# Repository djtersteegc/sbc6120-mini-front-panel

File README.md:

Project thread at https://forum.vcfed.org/index.php?threads/sbc6120-mini-front-panel.1245272/

# Switches

The current PCB and dress panel are drilled for miniature toggles with a 6mm diameter bushing/stem.  1/4-40 switches will NOT fit since I wanted a tight fit on the dress panel and the switches are spaced to tightly to use the dress nuts.  Plus, I think this style looks nicer (same as an Altair 8800).

These are commonly listed as MTS-102 (ON-ON) and MTS-112 (ON-Momentary ON) on AliExpress.  I tried all the different red and blue models and ended up using the red ones linked below in the BOM since they had exactly the same length toggles between the two different models.  Total cost shipped to the US for twenty MTS-102 and ten MTS-112 switches was less than ten bucks, versus the $40 it would cost to buy something like E-Switch 100 Series which was the cheapest domestic option I could find.  C&K 7000 series were over $160 for 20 miniature toggles.  Maybe the action is a bit better, but at the end of the day this is a toy for me, so I would personally rather spend the budget on the next project.

# Electrical BOM

There's an interactive BOM [here](https://djtersteegc.github.io/sbc6120-mini-front-panel/ibom.html), and CSV version with footprint info [here](https://djtersteegc.github.io/sbc6120-mini-front-panel/bom.csv).

I buy pretty much everything from UTSource (for logic) or AliExpress suppliers these days with the exception of the capacitors (whatever is on clearance at Newark) and the rotary switch is only available from C&K.  If you are shopping local everything should be available from Mouser/DigiKey/Newark.

Here is a [shared Mouser cart](https://www.mouser.com/ProjectManager/ProjectDetail.aspx?AccessID=54b04bab67) with all the electrical BOM minus the toggle and slide switches which are a China only part.

C16 is a bulk storage cap for the 5V line.  I specced it at 470uF, but anything from 100uF and up will probably be fine.  You may not even really need it.

| Component                                       | Qty  | Notes                | Link                                                         |
| ----------------------------------------------- | ---- | -------------------- | ------------------------------------------------------------ |
| 10nF Ceramic Capacitor                          | 1    | 5.08mm Lead Spacing  | [AliExpress](https://www.aliexpress.us/item/2251832786944590.html) |
| 100nF Ceramic Capacitor                         | 13   | 5.08mm Lead Spacing  | [AliExpress](https://www.aliexpress.us/item/2251832786944590.html) |
| 1uF Ceramic Capacitor                           | 1    | 5.08mm Lead Spacing  | [AliExpress](https://www.aliexpress.us/item/2251832786944590.html) |
| 470uF 16V Electrolytic Capacitor                | 1    | 3.5mm Lead Spacing   | [Newark](https://www.newark.com/multicomp-pro/mcmr16v477m8x9/cap-470uf-16v-alu-elec-radial/dp/39T1477) |
| 10K 1% 1/4W Resistor                            | 3    |                      | [AliExpress](https://www.aliexpress.us/item/2251832766343175.html) |
| 17.4K 1% 1/4W Resistor                          | 1    |                      | [AliExpress](https://www.aliexpress.us/item/2251832766343175.html) |
| 560R SIP9 Resistor Network                      | 4    | I used 510R          | [AliExpress](https://www.aliexpress.us/item/2251832653789055.html) |
| 4.7K SIP5 Resistor Network                      | 1    |                      | [AliExpress](https://www.aliexpress.us/item/2251832653789055.html) |
| 4.7K SIP6 Resistor Network                      | 1    |                      | [AliExpress](https://www.aliexpress.us/item/2251832653789055.html) |
| 4.7K SIP7 Resistor Network                      | 3    |                      | [AliExpress](https://www.aliexpress.us/item/2251832653789055.html) |
| 5mm LED (Red)                                   | 28   |                      | [AliExpress](https://www.aliexpress.us/item/2255800226642152.html) |
| Miniature ON-ON Toggle                          | 13   | MTS-102 - 6mm        | [AliExpress](https://www.aliexpress.us/item/3256805560180852.html) |
| Miniature ON-(ON) Momentary Toggle              | 7    | MTS-112 - 6mm        | [AliExpress](https://www.aliexpress.us/item/3256802276750993.html) |
| SPDT Right Angle Slide Switch                   | 3    | 2.54mm Spacing       | [AliExpress](https://www.aliexpress.us/item/2251832665517359.html) |
| C&K RM104772BCB Rotary Switch                   | 1    | 4 Position           | [Newark](https://www.newark.com/c-k-components/rm104772bcb/rotary-switch-1p-0-5a-24v-45deg/dp/69AH1990) |
| 74HC05                                          | 1    |                      |                                                              |
| 74HC74                                          | 1    |                      |                                                              |
| 74HC174                                         | 2    |                      |                                                              |
| 74HC366                                         | 4    |                      |                                                              |
| 74HC373                                         | 2    |                      |                                                              |
| 7555 Timer                                      | 1    |                      |                                                              |
| ATF16V8                                         | 1    |                      |                                                              |
| ATF22V10                                        | 1    |                      |                                                              |
| 2x25 2.54mm Pin Header                          | 1    |                      | [AliExpress](https://www.aliexpress.us/item/2251832485909733.html) |
| 1x2 2.54mm Pin Socket                           | 1    | Cut down a 40p strip | [AliExpress](https://www.aliexpress.us/item/2251832484668248.html) |
| 5.08mm 2p Terminal Block (or original 4P Molex) | 1    | KF301-2P (Power In)  | [AliExpress](https://www.aliexpress.us/item/2251832480927324.html) |

# Mechanical BOM

| Component                    | Qty  | Notes                | Link                                                         |
| ---------------------------- | ---- | -------------------- | ------------------------------------------------------------ |
| 12mm M3 Standoff             | 5    | SBC6120 to Panel     | 3D Print                                                     |
| 15.6mm M3 Standoff           | 7    | Panel to Dress Panel | 3D Print                                                     |
| 2mm High M3 Rubber Bumpers   | 7    | TS-2.7 Option        | [AliExpress](https://www.aliexpress.us/item/3256805089368820.html) |
| M3 x 6mm Taper Head Screws   | 12   |                      | [AliExpress](https://www.aliexpress.us/item/3256801858523146.html) |
| M3 x 12mm Taper Head Screws  | 5    |                      | [AliExpress](https://www.aliexpress.us/item/3256801858523146.html) |
| M2.5 x 6mm Taper Head Screws | 6    |                      | [AliExpress](https://www.aliexpress.us/item/3256801858523146.html) |
| 15mm Diameter Knob           | 1    | "Plum Shaft" Option  | [AliExpress](https://www.aliexpress.us/item/2251832788673272.html) |

# Other Parts

| Component                              | Notes              | Link                                                         |
| -------------------------------------- | ------------------ | ------------------------------------------------------------ |
| IDE to CF Adapater                     | CF-IDE40 or HX-168 | [AliExpress](https://www.aliexpress.us/item/3256804514420229.html) |
| DB9 to IDC 10                          | May need to rewire | [AliExpress](https://www.aliexpress.us/item/3256803077047244.html) |
| 5.5 x 2.1mm DC Input Jack for 8mm Hole | DC-025M            | [AliExpress](https://www.aliexpress.us/item/2255801022148508.html) |

# Case

The case is a simple two piece that holds the SBC6120 and front panel PCB securely to the bottom plate, and then the dress panel is held down by pressure around it's perimeter by the case top.  You will need supports on the bottom plate for CF, DB9, and DC power openings, but everything else can be printed without.  I would recommend a 0.2mm layer height since most dimensions are a multiple of that.  The case top and plate are 214mm x 135mm so they should be printable on something like a standard Ender 3.

Total PLA filament usage for all part is ~146 grams according to Cura 5.5.

| Part                              | Qty  | Filament Usage (PLA) |
| --------------------------------- | ---- | -------------------- |
| Case Top                          | 1    | 68g                  |
| Bottom Plate                      | 1    | 64g                  |
| Switch Spacer                     | 20   | 5g                   |
| M3 x 12mm Standoff                | 5    | 2g                   |
| M3 x 15.6mm Standoff              | 7    | 3g                   |
| Slide Switch                      | 3    | 1g                   |
| Reset Button                      | 1    | <1g                  |
| Rotary Knob Adapter               | 1    | 1g                   |
| 2.4mm Spacer for LED Installation | 4    | 1g                   |

Design file are in the [DesignSpark](3D/DesignSpark) folder if you would like to modify further or tweak tolerances for your printer. 

# Assembly

Build the PCB from low to high components, savings the switches, LED's, and pin headers for last. Pay attention to the Run (D28) LED, it's orientation is flipped vs. all the others. The rotary switch has a small notch, it MUST be lined up with the tick on the silkscreen. There is no other keying on this switch so it can be installed incorrectly.

Print out six copies of the [M3 x 15.6mm Standoff](3D/STL/M3%20x%2015.6mm%20Standoff.stl) if you are using the 2mm high rubber inserts on top of them, or use the [M3 x 17.6mm Standoff](3D/STL/M3%20x%2017.6mm%20Standoff.stl) if you are not.

Also print out 20 copies of the [Switch Spacer](3D/STL/Switch%20Spacer.stl).

Screw the standoff into the front panel PCB, place all the switches, paying attention to the ON-ON vs. ON-(ON) models. All momentary switches should face up with the exception of the Dep (SW19) which faces down when not activated.

Slip the 20 switch spacers onto the stems, and place the dress panel so it is resting on top of the standoffs and switch spacers.  It helps to have all the switches facing up (except for DEP), slip the panel over the DEP switch, and then rotate counterclockwise to drop over the rest of the switches.  Flip everything over and rest the dress panel on something to elevate it above your work surface so the switch stems hang down.  I found a 3/4" piece of plywood worked well for this.  While supporting the dress panel, push all the switch PCB lugs down so there is no slack between the top of the switch body, spacer, and dress panel.  This will give you a consistent reveal on the front panel even if the Chinese switch tolerances are a little off and/or switch won't sit flat on the PCB due to excess sealing epoxy applied on the bottom of it.  Solder them all in.  I did one terminal each, flipped over to check my work, and then did the rest.

For the LED's, remove the dress panel, drop in the 28 LED's (since I was using cheap Chinese one's I tested them all before to make sure they were all the same brightness, they were), and then flip everything over again until the LED's poke through the dress panel holes.  I elected to have 2.4mm of reveal/protrusion on the LED's, so print out four of the [2.4mm LED Spacer](3D/STL/2.4mm%20LED%20Spacer.stl) pucks and place them under the four corners of the dress panel.  Again, the 3/4" plywood allowed the panel to lay flat while the switches overhung the edge.  Solder one leg each on the LED's, flip over to check your work, and then do the others.

To install the pin headers first print and then install five [M3 x 12mm Standoff](3D/STL/M3%20x%2012mm%20Standoff.stl) on the SBC6120.  I went with 12mm instead of the more common 11mm since my socketed HD6120 was sitting at ~10mm and even after trimming the DIP socket and resistor network leads flush above it, it still seems a little tight for my tastes.  I also switched the CPREQ male header on the SBC6120 to a female header like the 2x25mm and that allowed me to fully install the male headers into both of them, and then place the front panel PCB on top and solder everything up. The header pins should be just flush with the top of the front panel PCB, not protruding like you would see with a normal install.

At this point you can install your IC's and make sure everything works.  JED files for the ATF16V8 and ATF22V10 are in the [Original STG FP6120 Files/pld](Original%20STG%20FP6120%20Files/pld) folder.  ATF16 gets decode.jed, ATF22 is control.jed. Now onto casing your new toy.

Plug the CF adapter, DB9, and DC input jack into the SBC6120.  Remove the 12mm standoffs, and install the SBC6120 to the [Bottom Plate](3D/STL/Bottom%20Plate%20-%20CF-IDE40.stl) with five M3x12mm screws into the bottom of the standoffs.

Slip three of the [Slide Switch](3D/STL/Slide%20Switch.stl) extenders onto the switches and install the front panel PCB onto the SBC6120.  Secure with five M3x6mm screws.

Angle the dress panel PCB into the [Top Case](3D/STL/Top%20Case.stl) and make sure it fits in the recess at the top.

Install the [Reset Button](3D/STL/Reset%20Button.stl) extender into the hole and then let the dress panel rest at the bottom of the top case on top of the six lugs for the screws. Place over the switches with a similar counterclockwise twisting motion as above, and then push the top case all the way down.

Secure with six M2.5x6mm screws through the bottom of the case.

Finally push the splined portion of the [Rotary Knob Adapter](3D/STL/Rotary%20Knob%20Adapter.stl) into your 6mm knob with the D cut opposite the indicator mark on the switch, and line up the D cut on the rotary switch.

# How do I get some PCB's?

If you are in the US, hit me up on the VCF forum thread above and if I have any extras, I can drop some in the mail for less than the cost of a small run at JLCPCB (size and shipping drive up the costs here).  Otherwise, there are gerber files available for use at your favorite PCB fab.

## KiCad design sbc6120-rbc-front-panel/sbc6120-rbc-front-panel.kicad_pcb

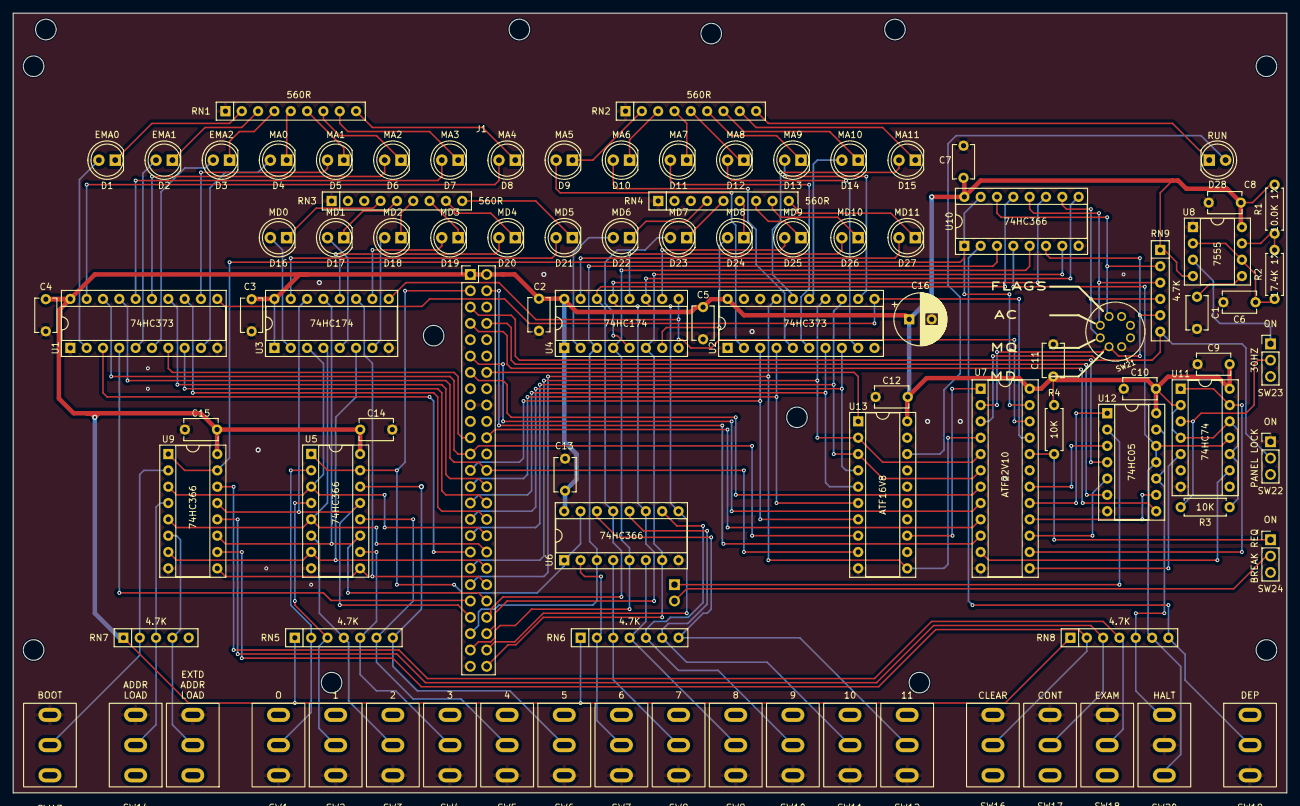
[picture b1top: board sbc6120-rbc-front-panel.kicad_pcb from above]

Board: 2 copper layers, 198.1 x 121.3 mm, 108 parts (1 on the bottom side), 139 nets.

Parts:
C1: 0.01UF; C_Disc_D5.1mm_W3.2mm_P5.00mm
C2, C3, C4, C5, C7, C8, C9, C10, C11, C12, C13, C14, C15: 100NF; C_Disc_D5.1mm_W3.2mm_P5.00mm
C6: 1UF 10V; C_Disc_D5.1mm_W3.2mm_P5.00mm
C16: 470uF 10V; CP_Radial_D8.0mm_P3.50mm
D1: EMA0; LED_D5.0mm
D2: EMA1; LED_D5.0mm
D3: EMA2; LED_D5.0mm
D4: MA0; LED_D5.0mm
D5: MA1; LED_D5.0mm
D6: MA2; LED_D5.0mm
D7: MA3; LED_D5.0mm
D8: MA4; LED_D5.0mm
D9: MA5; LED_D5.0mm
D10: MA6; LED_D5.0mm
D11: MA7; LED_D5.0mm
D12: MA8; LED_D5.0mm
D13: MA9; LED_D5.0mm
D14: MA10; LED_D5.0mm
D15: MA11; LED_D5.0mm
D16: MD0; LED_D5.0mm
D17: MD1; LED_D5.0mm
D18: MD2; LED_D5.0mm
D19: MD3; LED_D5.0mm
D20: MD4; LED_D5.0mm
D21: MD5; LED_D5.0mm
D22: MD6; LED_D5.0mm
D23: MD7; LED_D5.0mm
D24: MD8; LED_D5.0mm
D25: MD9; LED_D5.0mm
D26: MD10; LED_D5.0mm
D27: MD11; LED_D5.0mm
D28: RUN; LED_D5.0mm
H1, H2, H3, H4, H5, H6, H7, H8, H9, H10, H11, H12: MountingHole; MountingHole_3.2mm_M3_Bare
J1: Conn_02x25_Odd_Even; PinHeader_2x25_P2.54mm_Vertical
J2: SBC CPREQ; PinHeader_1x02_P2.54mm_Vertical
R1: 10.0K 1%; R_Axial_DIN0207_L6.3mm_D2.5mm_P7.62mm_Horizontal
R2: 17.4K 1%; R_Axial_DIN0207_L6.3mm_D2.5mm_P7.62mm_Horizontal
R3, R4: 10K; R_Axial_DIN0207_L6.3mm_D2.5mm_P7.62mm_Horizontal
RN1, RN2, RN3, RN4: 560R; R_Array_SIP9
RN5, RN6, RN8: 4.7K; R_Array_SIP7
RN7: 4.7K; R_Array_SIP5
RN9: 4.7K; R_Array_SIP6
SW1: SR0; Miniature Toggle Switch SPDT - Oval Holes
SW2: SR1; Miniature Toggle Switch SPDT - Oval Holes
SW3: SR2; Miniature Toggle Switch SPDT - Oval Holes
SW4: SR3; Miniature Toggle Switch SPDT - Oval Holes
SW5: SR4; Miniature Toggle Switch SPDT - Oval Holes
SW6: SR5; Miniature Toggle Switch SPDT - Oval Holes
SW7: SR6; Miniature Toggle Switch SPDT - Oval Holes
SW8: SR7; Miniature Toggle Switch SPDT - Oval Holes
SW9: SR8; Miniature Toggle Switch SPDT - Oval Holes
SW10: SR9; Miniature Toggle Switch SPDT - Oval Holes
SW11: SR10; Miniature Toggle Switch SPDT - Oval Holes
SW12: SR11; Miniature Toggle Switch SPDT - Oval Holes
SW13: BOOT; Miniature Toggle Switch SPDT - Oval Holes
SW14: LA; Miniature Toggle Switch SPDT - Oval Holes
SW15: LXA; Miniature Toggle Switch SPDT - Oval Holes
SW16: CLEAR; Miniature Toggle Switch SPDT - Oval Holes
SW17: CONT; Miniature Toggle Switch SPDT - Oval Holes
SW18: EXAM; Miniature Toggle Switch SPDT - Oval Holes
SW19: DEP; Miniature Toggle Switch SPDT - Oval Holes
SW20: HALT; Miniature Toggle Switch SPDT - Oval Holes
SW21: SP4T; RM104772BCB
SW22: PLOCK; PinHeader_1x03_P2.54mm_Vertical
SW23: 30HZ; PinHeader_1x03_P2.54mm_Vertical
SW24: ENABLE CONSOLE SLU BREAK REQ; PinHeader_1x03_P2.54mm_Vertical
U1, U2: 74HC373; DIP-20_W7.62mm_Socket
U3, U4: 74HC174; DIP-16_W7.62mm_Socket
U5, U6, U9, U10: 74HC366; DIP-16_W7.62mm_Socket
U7: ATF22V10; DIP-24_W7.62mm_Socket
U8: 7555; DIP-8_W7.62mm_Socket
U11: 74HC74; DIP-14_W7.62mm_Socket
U12: 74HC05; DIP-14_W7.62mm_Socket
U13: ATF16V8; DIP-20_W7.62mm_Socket

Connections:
/control-logic/HALT: RN8.5 (R4), SW20.3 (C), U12.10, U12.13
/control-logic/RUN: RN8.6 (R5), SW20.1 (A), U10.4 (I2), U11.11 (C), U12.11, U12.12
/control-logic/RUN LED H: D28.2 (A), U13.18 (IO2)
/control-logic/~AC DISP: RN9.3 (R2), SW21.3, U10.12 (I5)
/control-logic/~BOOT SW: RN7.2 (R1), SW13.2 (B), U9.2 (I1)
/control-logic/~CLEAR SW: RN8.2 (R1), SW16.2 (B), U9.10 (I4)
/control-logic/~CONSOLE BREAK REQ: R4.2, SW24.1 (A), U7.20 (IO4)
/control-logic/~CONT SW: RN8.3 (R2), SW17.2 (B), U9.12 (I5)
/control-logic/~CPREQ: J2.1, U12.2
/control-logic/~DEP SW: RN8.7 (R6), SW19.2 (B), U10.2 (I1)
/control-logic/~EXAM SW: RN8.4 (R3), SW18.2 (B), U9.14 (I6)
/control-logic/~LOAD ADDR SW: RN7.3 (R2), SW14.2 (B), U9.4 (I2)
/control-logic/~LOAD EXTD ADDR SW: RN7.4 (R3), SW15.2 (B), U9.6 (I3)
/control-logic/~MD DISP: RN9.5 (R4), SW21.1, U7.2 (I2), U10.6 (I3)
/control-logic/~MQ DISP: RN9.4 (R3), SW21.2, U10.10 (I4)
/control-logic/~PANEL LOCK: RN9.6 (R5), SW22.2 (B), U7.3 (I3)
/control-logic/~STATUS DISP: RN9.2 (R1), SW21.4, U10.14 (I6)
C0 L: J1.7, U12.8
C1 L: J1.8, U12.6
CLK ADDR DISP H: U1.11 (LE), U2.11 (LE), U7.21 (I03)
CLK DATA DISP H: U3.9 (Cp), U4.9 (Cp), U7.22 (IO2)
DX0: J1.34, U3.3 (D0), U5.3 (O1), U9.3 (O1)
DX1: J1.36, U3.4 (D1), U5.5 (O2), U9.5 (O2)
DX2: J1.38, U3.6 (D2), U5.7 (O3), U9.7 (O3)
DX3: J1.40, U3.11 (D3), U5.9 (O4), U9.9 (O4)
DX4: J1.42, U3.13 (D4), U5.11 (O5), U9.11 (O5)
DX5: J1.43, U3.14 (D5), U5.13 (O6), U9.13 (O6)
DX6: J1.45, U4.3 (D0), U6.3 (O1), U10.3 (O1)
DX7: J1.47, U4.4 (D1), U6.5 (O2), U10.5 (O2)
DX8: J1.50, U4.6 (D2), U6.7 (O3), U10.7 (O3)
DX9: J1.48, U4.11 (D3), U6.9 (O4), U10.9 (O4)
DX10: J1.46, U4.13 (D4), U6.11 (O5), U10.11 (O5)
DX11: J1.44, U4.14 (D5), U6.13 (O6), U10.13 (O6)
EMA0: J1.35, U1.3 (D0)
EMA1: J1.41, U1.4 (D1)
EMA2: J1.21, U1.7 (D2)
GND: C1.2, C2.2, C3.2, C4.2, C5.2, C6.2, C7.2, C8.2, C9.2, C10.2, C11.2, C12.2, C13.2, C14.2, C15.2, C16.2, J1.17, J1.18, J1.49, RN1.1 (common), RN2.1 (common), RN3.1 (common), RN4.1 (common), SW1.1 (A), SW2.1 (A), SW3.1 (A), SW4.1 (A), SW5.1 (A), SW6.1 (A), SW7.1 (A), SW8.1 (A), SW9.1 (A), SW10.1 (A), SW11.1 (A), SW12.1 (A), SW13.1 (A), SW14.1 (A), SW15.1 (A), SW16.1 (A), SW17.1 (A), SW18.1 (A), SW19.1 (A), SW20.2 (B), SW21.C, SW22.1 (A), U1.1 (OE), U1.10 (GND), U2.1 (OE), U2.10 (GND), U2.18 (D7), U3.8 (GND), U4.8 (GND), U5.8 (GND), U6.8 (GND), U7.12 (GND), U8.1 (GND), U9.8 (GND), U10.8 (GND), U11.7 (GND), U12.7 (GND), U13.10 (GND)
LXDAR L: J1.14, U13.1 (I1/CLK)
LXMAR L: J1.22, U7.9 (I9)
MA0: J1.30, U1.8 (D3)
MA1: J1.32, U1.13 (D4)
MA2: J1.28, U1.14 (D5)
MA3: J1.26, U1.17 (D6), U13.9 (I9)
MA4: J1.23, U1.18 (D7), U13.8 (I8)
MA5: J1.25, U2.3 (D0), U13.7 (I7)
MA6: J1.27, U2.4 (D1), U13.6 (I6)
MA7: J1.29, U2.7 (D2), U13.5 (I5)
MA8: J1.31, U2.8 (D3), U13.4 (I4)
MA9: J1.33, U2.13 (D4), U7.6 (I6), U13.3 (I3)
MA10: J1.37, U2.14 (D5), U7.5 (I5), U13.2 (I2)
MA11: J1.39, U2.17 (D6), U7.4 (I4), U13.11 (I10/~OE)
unnamed: D1.2 (A), U1.2 (O0)
unnamed: D1.1 (K), RN1.2 (R1)
unnamed: D2.2 (A), U1.5 (O1)
unnamed: D2.1 (K), RN1.3 (R2)
unnamed: D3.2 (A), U1.6 (O2)
unnamed: D3.1 (K), RN1.4 (R3)
unnamed: D4.2 (A), U1.9 (O3)
unnamed: D4.1 (K), RN1.5 (R4)
unnamed: D5.2 (A), U1.12 (O4)
unnamed: D5.1 (K), RN1.6 (R5)
unnamed: D6.2 (A), U1.15 (O5)
unnamed: D6.1 (K), RN1.7 (R6)
unnamed: D7.2 (A), U1.16 (O6)
unnamed: D7.1 (K), RN1.8 (R7)
unnamed: D8.2 (A), U1.19 (O7)
unnamed: D8.1 (K), RN1.9 (R8)
unnamed: D9.2 (A), U2.2 (O0)
unnamed: D9.1 (K), RN2.2 (R1)
unnamed: D10.2 (A), U2.5 (O1)
unnamed: D10.1 (K), RN2.3 (R2)
unnamed: D11.2 (A), U2.6 (O2)
unnamed: D11.1 (K), RN2.4 (R3)
unnamed: D12.2 (A), U2.9 (O3)
unnamed: D12.1 (K), RN2.5 (R4)
unnamed: D13.2 (A), U2.12 (O4)
unnamed: D13.1 (K), RN2.6 (R5)
unnamed: D14.2 (A), U2.15 (O5)
unnamed: D14.1 (K), RN2.7 (R6)
unnamed: D15.2 (A), U2.16 (O6)
unnamed: D15.1 (K), RN2.8 (R7)
unnamed: D16.2 (A), U3.2 (Q0)
unnamed: D16.1 (K), RN3.4 (R3)
unnamed: D17.2 (A), U3.5 (Q1)
unnamed: D17.1 (K), RN3.5 (R4)
unnamed: D18.2 (A), U3.7 (Q2)
unnamed: D18.1 (K), RN3.6 (R5)
unnamed: D19.2 (A), U3.10 (Q3)
unnamed: D19.1 (K), RN3.7 (R6)
unnamed: D20.2 (A), U3.12 (Q4)
unnamed: D20.1 (K), RN3.8 (R7)
unnamed: D21.2 (A), U3.15 (Q5)
unnamed: D21.1 (K), RN3.9 (R8)
unnamed: D22.2 (A), U4.2 (Q0)
unnamed: D22.1 (K), RN4.4 (R3)
unnamed: D23.2 (A), U4.5 (Q1)
unnamed: D23.1 (K), RN4.5 (R4)
unnamed: D24.2 (A), U4.7 (Q2)
unnamed: D24.1 (K), RN4.6 (R5)
unnamed: D25.2 (A), U4.10 (Q3)
unnamed: D25.1 (K), RN4.7 (R6)
unnamed: D26.2 (A), U4.12 (Q4)
unnamed: D26.1 (K), RN4.8 (R7)
unnamed: D27.2 (A), U4.15 (Q5)
unnamed: D27.1 (K), RN4.9 (R8)
unnamed: J2.2, SW24.2 (B)
unnamed: RN5.2 (R1), SW1.2 (B), U5.2 (I1)
unnamed: RN5.3 (R2), SW2.2 (B), U5.4 (I2)
unnamed: RN5.4 (R3), SW3.2 (B), U5.6 (I3)
unnamed: RN5.5 (R4), SW4.2 (B), U5.10 (I4)
unnamed: RN5.6 (R5), SW5.2 (B), U5.12 (I5)
unnamed: RN5.7 (R6), SW6.2 (B), U5.14 (I6)
unnamed: RN6.2 (R1), SW7.2 (B), U6.2 (I1)
unnamed: RN6.3 (R2), SW8.2 (B), U6.4 (I2)
unnamed: RN6.4 (R3), SW9.2 (B), U6.6 (I3)
unnamed: RN6.5 (R4), SW10.2 (B), U6.10 (I4)
unnamed: RN6.6 (R5), SW11.2 (B), U6.12 (I5)
unnamed: RN6.7 (R6), SW12.2 (B), U6.14 (I6)
unnamed: SW23.1 (A), U8.3 (Q)
unnamed: R3.2, SW23.2 (B), U11.3 (C)
unnamed: U7.18 (IO6), U12.3
unnamed: U7.17 (IO7), U12.1
unnamed: U7.16 (IO8), U12.9
unnamed: U7.15 (IO9), U12.5
unnamed: C1.1, U8.5 (CV)
unnamed: R1.2, R2.1, U8.7 (DIS)
unnamed: C6.1, R2.2, U8.2 (TR), U8.6 (THR)
unnamed: U7.23 (IO1), U9.1 (E1), U9.15 (E2), U10.1 (E1), U10.15 (E2)
unnamed: U7.13 (I12), U11.5 (Q)
unnamed: U7.14 (IO10), U11.1 (~R), U11.13 (~R)
unnamed: U7.11 (I11), U11.9 (Q)
unnamed: U7.1 (I1/CLK), U13.13 (IO7)
RD SR L: J1.3, U5.1 (E1), U5.15 (E2), U6.1 (E1), U6.15 (E2)
READ L: J1.11, U7.8 (I8)
RUN LED: D28.1 (K), RN2.9 (R8)
SKIP L: J1.5, U12.4
VCC: C2.1, C3.1, C4.1, C5.1, C7.1, C8.1, C9.1, C10.1, C11.1, C12.1, C13.1, C14.1, C15.1, C16.1, J1.1, J1.2, R1.1, R3.1, R4.1, RN5.1 (common), RN6.1 (common), RN7.1 (common), RN8.1 (common), RN9.1 (common), U1.20 (VCC), U2.20 (VCC), U3.1 (~Mr), U3.16 (VCC), U4.1 (~Mr), U4.16 (VCC), U5.16 (VCC), U6.16 (VCC), U7.24 (VCC), U8.4 (R), U8.8 (VCC), U9.16 (VCC), U10.16 (VCC), U11.2 (D), U11.4 (~S), U11.10 (~S), U11.12 (D), U11.14 (VCC), U12.14 (VCC), U13.20 (VCC)
WR SR L: J1.4, U7.10 (I10)
WRITE L: J1.13, U7.7 (I7)

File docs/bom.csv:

"#","Reference","Qty","Value","Footprint","DNP"
"1","C1","1","0.01UF","Capacitor_THT:C_Disc_D5.1mm_W3.2mm_P5.00mm",""
"2","C2, C3, C4, C5, C7, C8, C9, C10, C11, C12, C13, C14, C15","13","100NF","Capacitor_THT:C_Disc_D5.1mm_W3.2mm_P5.00mm",""
"3","C6","1","1UF 10V","Capacitor_THT:C_Disc_D5.1mm_W3.2mm_P5.00mm",""
"4","C16","1","470uF 10V","Capacitor_THT:CP_Radial_D8.0mm_P3.50mm",""
"5","D1","1","EMA0","LED_THT:LED_D5.0mm",""
"6","D2","1","EMA1","LED_THT:LED_D5.0mm",""
"7","D3","1","EMA2","LED_THT:LED_D5.0mm",""
"8","D4","1","MA0","LED_THT:LED_D5.0mm",""
"9","D5","1","MA1","LED_THT:LED_D5.0mm",""
"10","D6","1","MA2","LED_THT:LED_D5.0mm",""
"11","D7","1","MA3","LED_THT:LED_D5.0mm",""
"12","D8","1","MA4","LED_THT:LED_D5.0mm",""
"13","D9","1","MA5","LED_THT:LED_D5.0mm",""
"14","D10","1","MA6","LED_THT:LED_D5.0mm",""
"15","D11","1","MA7","LED_THT:LED_D5.0mm",""
"16","D12","1","MA8","LED_THT:LED_D5.0mm",""
"17","D13","1","MA9","LED_THT:LED_D5.0mm",""
"18","D14","1","MA10","LED_THT:LED_D5.0mm",""
"19","D15","1","MA11","LED_THT:LED_D5.0mm",""
"20","D16","1","MD0","LED_THT:LED_D5.0mm",""
"21","D17","1","MD1","LED_THT:LED_D5.0mm",""
"22","D18","1","MD2","LED_THT:LED_D5.0mm",""
"23","D19","1","MD3","LED_THT:LED_D5.0mm",""
"24","D20","1","MD4","LED_THT:LED_D5.0mm",""
"25","D21","1","MD5","LED_THT:LED_D5.0mm",""
"26","D22","1","MD6","LED_THT:LED_D5.0mm",""
"27","D23","1","MD7","LED_THT:LED_D5.0mm",""
"28","D24","1","MD8","LED_THT:LED_D5.0mm",""
"29","D25","1","MD9","LED_THT:LED_D5.0mm",""
"30","D26","1","MD10","LED_THT:LED_D5.0mm",""
"31","D27","1","MD11","LED_THT:LED_D5.0mm",""
"32","D28","1","RUN","LED_THT:LED_D5.0mm",""
"33","H1, H2, H3, H4, H5, H6, H7, H8, H9, H10, H11, H12","12","MountingHole","Tersteeg:MountingHole_3.2mm_M3_Bare",""
"34","J1","1","Conn_02x25_Odd_Even","Connector_PinHeader_2.54mm:PinHeader_2x25_P2.54mm_Vertical",""
"35","J2","1","SBC CPREQ","Connector_PinHeader_2.54mm:PinHeader_1x02_P2.54mm_Vertical",""
"36","R1","1","10.0K 1%","Resistor_THT:R_Axial_DIN0207_L6.3mm_D2.5mm_P7.62mm_Horizontal",""
"37","R2","1","17.4K 1%","Resistor_THT:R_Axial_DIN0207_L6.3mm_D2.5mm_P7.62mm_Horizontal",""
"38","R3, R4","2","10K","Resistor_THT:R_Axial_DIN0207_L6.3mm_D2.5mm_P7.62mm_Horizontal",""
"39","RN1, RN2, RN3, RN4","4","560R","Resistor_THT:R_Array_SIP9",""
"40","RN5, RN6, RN8","3","4.7K","Resistor_THT:R_Array_SIP7",""
"41","RN7","1","4.7K","Resistor_THT:R_Array_SIP5",""
"42","RN9","1","4.7K","Resistor_THT:R_Array_SIP6",""
"43","SW1","1","SR0","Tersteeg:Miniature Toggle Switch SPDT - Oval Holes",""
"44","SW2","1","SR1","Tersteeg:Miniature Toggle Switch SPDT - Oval Holes",""
"45","SW3","1","SR2","Tersteeg:Miniature Toggle Switch SPDT - Oval Holes",""
"46","SW4","1","SR3","Tersteeg:Miniature Toggle Switch SPDT - Oval Holes",""
"47","SW5","1","SR4","Tersteeg:Miniature Toggle Switch SPDT - Oval Holes",""
"48","SW6","1","SR5","Tersteeg:Miniature Toggle Switch SPDT - Oval Holes",""
"49","SW7","1","SR6","Tersteeg:Miniature Toggle Switch SPDT - Oval Holes",""
"50","SW8","1","SR7","Tersteeg:Miniature Toggle Switch SPDT - Oval Holes",""
"51","SW9","1","SR8","Tersteeg:Miniature Toggle Switch SPDT - Oval Holes",""
"52","SW10","1","SR9","Tersteeg:Miniature Toggle Switch SPDT - Oval Holes",""
"53","SW11","1","SR10","Tersteeg:Miniature Toggle Switch SPDT - Oval Holes",""
"54","SW12","1","SR11","Tersteeg:Miniature Toggle Switch SPDT - Oval Holes",""
"55","SW13","1","BOOT","Tersteeg:Miniature Toggle Switch SPDT - Oval Holes",""
"56","SW14","1","LA","Tersteeg:Miniature Toggle Switch SPDT - Oval Holes",""
"57","SW15","1","LXA","Tersteeg:Miniature Toggle Switch SPDT - Oval Holes",""
"58","SW16","1","CLEAR","Tersteeg:Miniature Toggle Switch SPDT - Oval Holes",""
"59","SW17","1","CONT","Tersteeg:Miniature Toggle Switch SPDT - Oval Holes",""
"60","SW18","1","EXAM","Tersteeg:Miniature Toggle Switch SPDT - Oval Holes",""
"61","SW19","1","DEP","Tersteeg:Miniature Toggle Switch SPDT - Oval Holes",""
"62","SW20","1","HALT","Tersteeg:Miniature Toggle Switch SPDT - Oval Holes",""
"63","SW21","1","RM104772BCB","RM104772BCB-SnapEDA:RM104772BCB",""
"64","SW22","1","PLOCK","Connector_PinHeader_2.54mm:PinHeader_1x03_P2.54mm_Vertical",""
"65","SW23","1","30HZ","Connector_PinHeader_2.54mm:PinHeader_1x03_P2.54mm_Vertical",""
"66","SW24","1","ENABLE CONSOLE SLU BREAK REQ","Connector_PinHeader_2.54mm:PinHeader_1x03_P2.54mm_Vertical",""
"67","U1, U2","2","74HC373","Package_DIP:DIP-20_W7.62mm_Socket",""
"68","U3, U4","2","74HC174","Package_DIP:DIP-16_W7.62mm_Socket",""
"69","U5, U6, U9, U10","4","74HC366","Package_DIP:DIP-16_W7.62mm_Socket",""
"70","U7","1","ATF22V10","Package_DIP:DIP-24_W7.62mm_Socket",""
"71","U8","1","7555","Package_DIP:DIP-8_W7.62mm_Socket",""
"72","U11","1","74HC74","Package_DIP:DIP-14_W7.62mm_Socket",""
"73","U12","1","74HC05","Package_DIP:DIP-14_W7.62mm_Socket",""
"74","U13","1","ATF16V8","Package_DIP:DIP-20_W7.62mm_Socket",""

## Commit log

2023-12-17 Version 1.0
2023-12-17 Add image
2023-12-17 Update docs
2023-12-18 Fix hole size
2023-12-18 Fix README
2023-12-18 Fix BOM
2023-12-18 Add Mouser shared cart
2023-12-19 Update 3D printing info
2023-12-19 Fix BOM link typo
2023-12-20 Case tweaks:
    Improve slide switch action
    Increase lug size to move screw holes away from outer edge
    Add lip on base to help center top during assembly
    Tighten tolerance from 0.5mm to 0.3mm for dress panel recess
    Add supports under switch area for front panel
    Add forward stop and right side support for CF card adapter
